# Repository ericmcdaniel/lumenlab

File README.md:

<p align="center">
  <picture>
    <source media="(prefers-color-scheme: dark)" srcset="assets/lumenlab-logo-dark.png">
    <source media="(prefers-color-scheme: light)" srcset="assets/lumenlab-logo.png">
    
  </picture>
</p>
<p align="center">Transforming pixels into a playground</p>

---

__LumenLab__ is an LED strip gaming and entertainment platform designed to transform your space into an interactive playground of light. Powered by an ESP32 microcontroller, displayed through a NeoPixel addressable LED strip, and controlled by a PlayStation 3 game controller, LumenLab brings simple, one-dimensional retro arcade-style games, animations, and ambient lighting to life.
<br>

# Features

LumenLab is composed of two modes. The central mode is its suite of games, but the platform also supports animations and ambient lighting, called scenes. After all it's still an LED strip!

## Games
Using an LED strip as a gaming platform is a unique concept due to the constraint of only having one dimension to interact with. Since *only* the landscape x-axis is available, this constraint compels players to apply creative interpretation during gameplay. This of course is not a modern, feature rich AAA blockbuster with 4K graphics, immersing you in the vision of a world crafted by others. Instead, LumenLab's restriction subtly encourages players to philosophically revisit what it *really* means to play a game down to the core. In its purest form, a game player follows rules and explores boundaries in pursuit of a goal. Gamers encounter conflict and must experiment and adapt to their environment to overcome obstacles. LumenLab forces players to abstractly experience digital gaming at its rawest, most atomic form: structured uncertainty and strategy until mastery is achieved. This has become the manifesto of the LumenLab. **Every individual playing its games has a unique mental concept of what they're experiencing.**

Because LumenLab is restricted to a single dimension composed of an array of LEDs, it's aesthetically reminiscent of retro arcade games. However, LumenLab exploits capabilities unavailable on old 8-bit game consoles. These capabilities include its ability to generate any arbitrary RGB color instead of being limited to 256 colors. Additionally, its UI takes advantage of the broad range of controls and state offered by the PS3 controller such as the number of buttons available and precise analog joy stick/trigger positions, contrasting from a cabinet arcade with only four discrete buttons. There are over six games, each detailed below.

| **Title** | **Description** |
| --- | --- |
| **Recall** | *Recall* is a fast-paced memory game inspired by Hasbro’s classic game [*Simon*](https://en.wikipedia.org/wiki/Simon_(game)). The LED strip flashes a growing sequence of colors, and the player must repeat it correctly using X, Circle, Triangle, and Square buttons of their PS3 controller. |
| **Phase Evasion** | *Phase Evasion* is a fast-paced reflex game where you shift your color to phase through incoming flares. Grab scattered gems for bonus points as the speed increases and the challenge intensifies. |
| **Light Strike** | *Light Strike* combines the spirit of Atari's [*Space Invaders*](https://en.wikipedia.org/wiki/Space_Invaders) with elements of [*Asteroids*](https://en.wikipedia.org/wiki/Asteroids_(video_game)). As a lone agent in deep space, you enounter waves of predators approaching you from directions sides at varying speeds. Moving freely across the x-axis, and your survival requires defending yourself with your laser pistol. Conserve your ammunition however, your weapon can only fire so many rounds a minute!<br><br>*In development.* |
| **Reflex** | *Reflex* is a fast-moving inspired by the modern arcade game [*Pop the Lock*](https://www.baytekent.com/pop-the-lock/), testing precision and timing under pressure. A moving marker sweeps across the field toward a shifting target. Fire at the perfect moment to score a hit. Each success quickens the pace, reverses the marker's direction, and relocates the target to a new random location. Survive fifty flawless shots to win.<br><br>*In development.* |
| **Spectrum** | *Spectrum* tests your perception of color and precision of control. A random RGB color appears on one end of the display, and you must use the analog stick to recreate it as closely as possible. The closer your match, the higher your score.<br><br>*In development* |
| **Pursuit** | *In development.* Details to be provided soon. |

There are more game ideas in the works, and ideas for some *two-player* games are being considered.

## Scenes

An LED strip entertainment platform would not be complete if it did not include animations and special effects libraries. Inspired by the [WLED project](https://kno.wled.ge/), LumenLab is able to create captivating scenes. Many of them are interactive, for example moving the joystick can change the color, or pressing the directional buttons can change timing.
| **Title** | **Description** |
| --- | --- |
| **Canvas** | *Canvas* lets you choose any color across the RGB range, turning the LED strip into a fully color-customized ambient light source. Press **L1** to rebalance the saturation, **R1** to rebalance the lightness, and **Triangle** to switch to a new random color. |
| **Tempo** | *Tempo* allows you to choose a tempo and strobe lights and trigger light subroutines in response to music.<br><br>*In development.* |
| **Police Siren** | Strobing red and blue lights to look like a law enforcement vehicle.<br><br>*In development.* |
| **Halloween** | Spooky orange and some purple.<br><br>*In development.* |
| **Christmas** | Festive red and green.<br><br>*In development.* |

And more to come.

---

# Experience the Lights in Your Home
Being a hardware-forward project, it is not possible to experience LumenLab without physically having the device. Your options include either having a PCB professionally manufactured and assembled, or soldering your own prototype on a breadboard or perf board using off-the-shelf components.

This guide will walk through both options and their practicality.

## Method A: Professionally Manufactured and Assembled

A custom PCB was designed using KiCad 9 and gives LumenLab a clean aesthetic. All of the schematic files, PCB layout files, BOM, custom symbol libraries, footprints, 3D models, and Gerber files are all found in the [/hardware](./hardware/) directory. The PCB layout uses the manufacturing capabilities given by [PCBWay](https://www.pcbway.com/). Although you can potentially use any board house of your choosing, the ECAD model was designed with PCBWay's capabilities in mind. Production costs were minimized as much as safely reasonable, such as keeping it's width under 100mm. However for the amount of current that it can potentially consume, thermal safety was factored in, leading to a four-layer design with extra forgiving trace width and copper pours. My manufacturing costs were roughly $50 for ten boards. If you choose to have this manufactured else where, you must adjust for the capabilities of that board house. Your mileage may vary, and by quite a bit too.

<p align="center"><i>Figure 1: Front of PCB layout</i></p>

You can view the KiCad schematic, PCB layout, BOM, and 3D rendering of the PCB design [in the *board* directory.](./hardware/)

## Method B: Hand-Soldering a Prototype

This is the more accessible and classic route especially for DIY enthusiasts, however this can be tricky depending on your background with electronics. Below is the prototype BOM if you'd like to build LumenLab yourself using pre-built modules, THT components, and a breadboard or perfboard. If you're an advanced electronics enthusiast, you may even be able to omit some of the suggestions, such as skipping the buck converter, directly powering the LED strip, and using the 5V power directly from the Vin pin to level shift the LED strip's data signal. These "barebones" alterations are not discussed in this document.

Assembly is remarkably similar to the guidance given on the WLED project. Using their [wiring diagram here](https://kno.wled.ge/basics/wiring-guides/) would be an excellent starting point.

#### <center>Bill of Materials</center>
|  Device | Description |
| --- | --- |
| ESP32 WROOM microcontroller | Only the [WROOM variants](https://docs.espressif.com/projects/esp-dev-kits/en/latest/esp32/esp32-devkitc/index.html) are supported because those are the only variants that support the Bluetooth classic protocol (BR/EDR). You **cannot** substitude the WROOM with other variants, as they all only have support for BLE. |
| WS2815 LED light strip | The 12V variant of the NeoPixel addressable RGB WS2812B. This project uses the 5m (16.4ft), 300 LED strip in black. |
| 12V 10A DC power supply | The 10A supply is required due to the high current demands of displaying white at full brightness. 120W is only the peak power draw, but this typically runs much lower. |
| MP2338 buck converter | Any step down regulator will suffice as long as it outputs 5V and at least 1A. The MP2338 can deliver 2-3A, enough to reliable power the ESP32 during intense gameplay and Bluetooth connectivity. |
| SN74AHCT125N logic level shifter | The ESP32's GPIO lines work using 3.3V signals. Level shifting to 5V ensures that the LED strip's data lines are not lost or corrupted. |
| PlayStation 3 game controller | The input device to navigate the main menu and play games. |
| SSD1306 OLED display module | Using the 0.96" variant, this displays the main menu for mode selection and in game mode is a HUD showing basic statistic like the user's high score. |
| Passive components | Resistors, capacitors, diodes, and fuses as needed for power protection, power stability and smoothing, low-pass filtering, and signal damping to minimize ringing. Refer to your MCU and buck converter's datasheet for guidance on what passives are needed. |

# Software

Regardless of whether your build of LumenLab was professionally manufactured and assembled, or hand-soldered to a perf board, the software is identical between the two approaches. To build this project from scratch, you at minimum need the following frameworks and dependencies:

* **PlatformIO**: A feature-rich ecosystem for embedded development. This framework includes the C/C++ compiler (avr-gcc) needed for MCU development. You can use the toolchain CLI directly, but installing the Visual Studio Code extension is significantly more approachable. [Download PlatformIO here](https://platformio.org/).
* **Python3** (&GreaterEqual;3.6): A dependency of PlatformIO to compile and flash the device. Also used in the virtualizer for local development.

## LED Strip Virtualization

To streamline the software development cycle, a virtualizer was created so that you can simulate what the LEDs would be displaying, but on your computer screen. This enables new features to be developed in comfort without needing to physically connect to the LED strip. Using the ESP32 is still required for development regardless since it's just an emulator for what the ESP32 is actually doing in real time.

When compiling in debug mode, the ESP32 does not transmit color signals to the LED strip and instead sends its color data via USB serial for virtual rendering. When compiling in release mode, the virtualizer and logs are removed. This virtualizer was created using Python, and uses the [ModernGL](https://moderngl.readthedocs.io/en/5.8.2/) library, an OpenGL binding for Python.

<p align="center"><i>Figure 2: Development Virtualizer of two controllable entities, simulating what the LED strip would be rendering</i></p>

## Building the Repository
This section was redacted temporarily because of how rapidly the code base is evolving. The instructions I wrote no longer apply as the Virtualizer was rewritten for speed to send color data via a USB serial connection instead of an open WebSocket connection. Stay tuned.

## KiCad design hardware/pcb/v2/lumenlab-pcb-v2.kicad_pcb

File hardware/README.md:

# Custom PCB Fabrication

The LumenLab was built in two phases. The first phase (labeled as "Version 1") was a prototype that used through-hole components hand-soldered on to several perf boards. This was a good start, especially for making progress in the early stages of the software development, however the components did not work exactly as desired, making its maintanance more of a hassle than it was a benefit. Designing a PCB to be professionally manufactured became a clear and obvious choice, allowing the LumenLab to be scaled into a clean, stable device.

The LumenLab PCB was designed using KiCad 9.0.5

# Schematic

<p align="center"><i>Figure 1. LumenLab schematic and electronic layout</i></p>

# Bill of Materials
Still to be finalized, however you can [view the tentative list of components here](./v1/bom/ibom.html).

# PCB Layout

<p align="center"><i>Figure 2: PCB layout</i></p>

# 3D Preview

<p align="center"><i>Figure 3: PCB 3D preview</i></p>

A 3D printed enclosure will be created to give the final device a clean look.

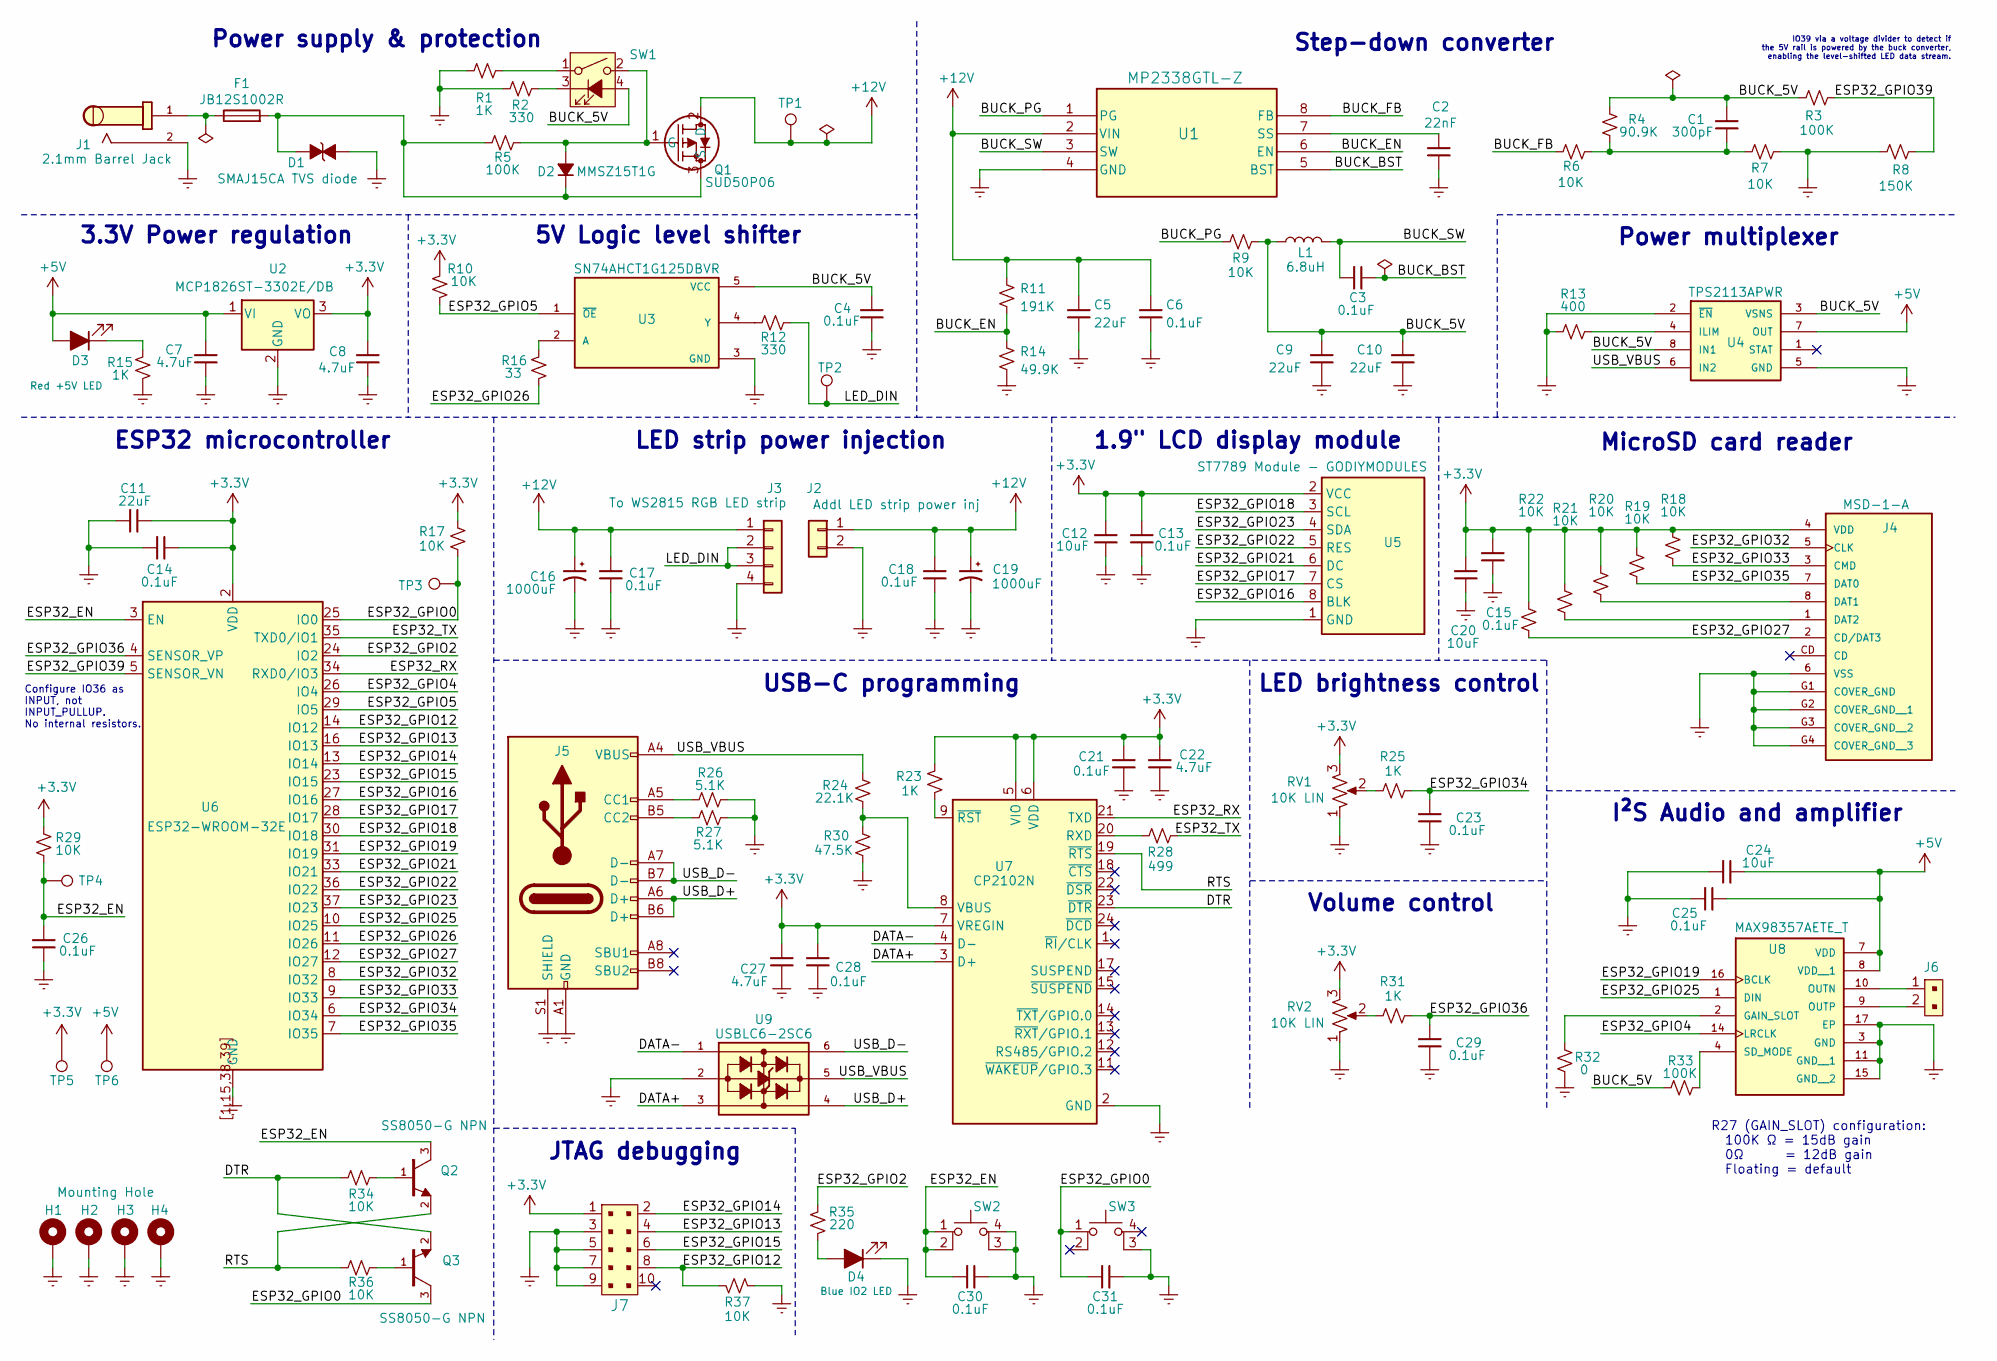
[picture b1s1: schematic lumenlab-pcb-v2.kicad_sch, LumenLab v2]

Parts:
C1: 300pF; C_0603_1608Metric_Pad1.08x0.95mm_HandSolder
C2: 22nF; C_0603_1608Metric_Pad1.08x0.95mm_HandSolder
C3, C4, C6, C13, C14, C15, C17, C18, C21, C23, C25, C26, C28, C29, C30, C31: 0.1uF; C_0603_1608Metric_Pad1.08x0.95mm_HandSolder
C5, C9, C10, C11: 22uF; C_1210_3225Metric_Pad1.33x2.70mm_HandSolder
C7, C8: 4.7uF; C_1206_3216Metric_Pad1.33x1.80mm_HandSolder
C12, C20: 10uF; C_0603_1608Metric_Pad1.08x0.95mm_HandSolder
C16, C19: 1000uF; CP_Radial_D10.0mm_P5.00mm
C22, C27: 4.7uF; C_0805_2012Metric_Pad1.18x1.45mm_HandSolder
C24: 10uF; C_1206_3216Metric_Pad1.33x1.80mm_HandSolder
D1: SMAJ15CA TVS diode; SMASeries_LTF-M
D2: MMSZ15T1G; D_SOD-123
D3: Red +5V LED; LED_0805_2012Metric_Pad1.15x1.40mm_HandSolder
D4: Blue IO2 LED; LED_0805_2012Metric_Pad1.15x1.40mm_HandSolder
F1: JB12S1002R; Fuse_1206_3216Metric_Pad1.42x1.75mm_HandSolder
H1: Mounting Hole; MountingHole_3.2mm_M3_Pad
H2, H3, H4: MountingHole; MountingHole_3.2mm_M3_Pad
J1: 2.1mm Barrel Jack; CONN_SD-172448-0000_02_MOL; PARTREV A
J2: Addl LED strip power inj; CONN_SD-172448-0000_02_MOL
J3: To WS2815 RGB LED strip; CONN_SD-172448-0000_04_MOL
J4: MSD-1-A; CUI_MSD-1-A; PARTREV 1.0
J5: USB_C_Receptacle_USB2.0_16P; USB_C_Receptacle_JAE_DX07S016JA1R1500
J6: B2B-XH-A_LF__SN_; JST_XH_B2B-XH-A_1x02_P2.50mm_Vertical; MPN B2B-XH-A(LF)(SN); Digi-Key_PN 455-2247-ND
J7: JTAG; PinHeader_2x5_P1.27mm_Drill.7mm; MPN 3220-10-0100-00; Digi-Key_PN 1175-1627-ND
L1: 6.8uH; IND_MGAH06036R8M-10
Q1: SUD50P06; PMOSGDS_D-PAKTO-252AA_VIS-L
Q2, Q3: SS8050-G NPN; TRANS_SS8050-G; PARTREV A
R1, R15, R23, R25, R31: 1K; R_0603_1608Metric_Pad0.98x0.95mm_HandSolder
R2, R12: 330; R_0603_1608Metric_Pad0.98x0.95mm_HandSolder
R3, R5, R33: 100K; R_0603_1608Metric_Pad0.98x0.95mm_HandSolder
R4: 90.9K; R_0603_1608Metric_Pad0.98x0.95mm_HandSolder
R6, R7, R9, R10, R17, R18, R19, R20, R21, R22, R29, R34, R36, R37: 10K; R_0603_1608Metric_Pad0.98x0.95mm_HandSolder
R8: 150K; R_0603_1608Metric_Pad0.98x0.95mm_HandSolder
R11: 191K; R_0603_1608Metric_Pad0.98x0.95mm_HandSolder
R13: 400; R_0603_1608Metric_Pad0.98x0.95mm_HandSolder
R14: 49.9K; R_0603_1608Metric_Pad0.98x0.95mm_HandSolder
R16: 33; R_0603_1608Metric_Pad0.98x0.95mm_HandSolder
R24: 22.1K; R_0603_1608Metric_Pad0.98x0.95mm_HandSolder
R26, R27: 5.1K; R_0603_1608Metric_Pad0.98x0.95mm_HandSolder
R28: 499; R_0603_1608Metric_Pad0.98x0.95mm_HandSolder
R30: 47.5K; R_0603_1608Metric_Pad0.98x0.95mm_HandSolder
R32: 0; R_0603_1608Metric_Pad0.98x0.95mm_HandSolder
R35: 220; R_0603_1608Metric_Pad0.98x0.95mm_HandSolder
RV1, RV2: 10K LIN; JST_XH_B3B-XH-A_1x03_P2.50mm_Vertical
SW1: SW_DPST; JST_XH_B4B-XH-A_1x04_P2.50mm_Vertical
SW2: RESET; SW_TS18-5-15-SL-160-SMT-TR
SW3: BOOT; SW_TS18-5-15-SL-160-SMT-TR
TP1: +12V; TestPoint_THTPad_D2.0mm_Drill1.0mm
TP2: LED_SIG; TestPoint_THTPad_D2.0mm_Drill1.0mm
TP3: IO0; TestPoint_THTPad_D2.0mm_Drill1.0mm
TP4: EN; TestPoint_THTPad_D2.0mm_Drill1.0mm
TP5: +3.3V; TestPoint_THTPad_D2.0mm_Drill1.0mm
TP6: +5V; TestPoint_THTPad_D2.0mm_Drill1.0mm
U1: MP2338GTL-Z; MP2338_MNP-M
U2: MCP1826ST-3302E/DB; SOT-223-3_TabPin2
U3: SN74AHCT1G125DBVR; SOT95P280X145-5N
U4: TPS2113APWR; SOP65P640X120-8N
U5: ST7789 Module - GODIYMODULES; JST_XH_B8B-XH-A_1x08_P2.50mm_Vertical
U6: ESP32-WROOM-32E
U7: CP2102N; QFN-24-1EP_4x4mm_P0.5mm_EP2.15x2.15mm
U8: MAX98357AETE_T; QFN50P300X300X80-17N
U9: USBLC6-2SC6; SOT95P280X145-6N

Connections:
+3.3V: C8.1, C11.1, C12.2, C13.2, C14.2, C15.2, C20.2, C21.1, C22.1, C27.1, C28.1, J4.4 (VDD), J7.1, R10.1, R17.1, R18.2, R19.2, R20.2, R21.2, R22.2, R23.2, R29.1, RV1.3, RV2.3, TP5.1 (1_1), U2.3 (VO), U5.2 (VCC), U6.2 (VDD), U7.5 (VIO), U7.6 (VDD), U7.7 (VREGIN)
+5V: C7.1, C24.1, C25.1, D3.2 (A), TP6.1 (1_1), U2.1 (VI), U4.7 (OUT), U8.7 (VDD), U8.8 (VDD__1)
+12V: C5.1, C6.1, C16.1, C17.1, C18.1, C19.1, J2.1, J3.1, Q1.2 (D), R11.1, TP1.1 (1_1), U1.2 (VIN)
/BUCK_5V: C1.2, C4.2, C9.1, C10.1, L1.1, R3.1, R4.2, R9.2, R33.1, SW1.4 (A), U3.5 (VCC), U4.3 (VSNS), U4.8 (IN1)
/BUCK_BST: C3.1, U1.5 (BST)
/BUCK_EN: R11.2, R14.1, U1.6 (EN)
/BUCK_FB: R6.1, U1.8 (FB)
/BUCK_PG: R9.1, U1.1 (PG)
/BUCK_SW: C3.2, L1.2, U1.3 (SW)
/DATA+: U7.3 (D+), U9.3
/DATA-: U7.4 (D-), U9.1
/DTR: Q3.2, R34.1, U7.23 (~DTR)
/ESP32_EN: C26.1, C30.2, Q2.3, R29.2, SW2.1, SW2.2, TP4.1 (1_1), U6.3 (EN)
/ESP32_GPIO0: C31.2, Q3.3, R17.2, SW3.1, TP3.1 (1_1), U6.25 (IO0)
/ESP32_GPIO2: R35.1, U6.24 (IO2)
/ESP32_GPIO4: U6.26 (IO4), U8.14 (LRCLK)
/ESP32_GPIO5: R10.2, U3.1 (~OE), U6.29 (IO5)
/ESP32_GPIO12: J7.8, R37.1, U6.14 (IO12)
/ESP32_GPIO13: J7.4, U6.16 (IO13)
/ESP32_GPIO14: J7.2, U6.13 (IO14)
/ESP32_GPIO15: J7.6, U6.23 (IO15)
/ESP32_GPIO16: U5.8 (BLK), U6.27 (IO16)
/ESP32_GPIO17: U5.7 (CS), U6.28 (IO17)
/ESP32_GPIO18: U5.3 (SCL), U6.30 (IO18)
/ESP32_GPIO19: U6.31 (IO19), U8.16 (BCLK)
/ESP32_GPIO21: U5.6 (DC), U6.33 (IO21)
/ESP32_GPIO22: U5.5 (RES), U6.36 (IO22)
/ESP32_GPIO23: U5.4 (SDA), U6.37 (IO23)
/ESP32_GPIO25: U6.10 (IO25), U8.1 (DIN)
/ESP32_GPIO26: R16.2, U6.11 (IO26)
/ESP32_GPIO27: J4.2 (CD/DAT3), R22.1, U6.12 (IO27)
/ESP32_GPIO32: J4.5 (CLK), U6.8 (IO32)
/ESP32_GPIO33: J4.3 (CMD), R18.1, U6.9 (IO33)
/ESP32_GPIO34: C23.2, R25.2, U6.6 (IO34)
/ESP32_GPIO35: J4.7 (DAT0), R19.1, U6.7 (IO35)
/ESP32_GPIO36: C29.2, R31.2, U6.4 (SENSOR_VP)
/ESP32_GPIO39: R3.2, R8.1, U6.5 (SENSOR_VN)
/ESP32_RX: U6.34 (RXD0/IO3), U7.21 (TXD)
/ESP32_TX: R28.1, U6.35 (TXD0/IO1)
/LED_DIN: J3.2, J3.3, R12.2, TP2.1 (1_1)
/RTS: Q2.2, R36.1, U7.19 (~RTS)
/USB_D+: J5.A6 (D+), J5.B6 (D+), U9.4
/USB_D-: J5.A7 (D-), J5.B7 (D-), U9.6
/USB_VBUS: J5.A4 (VBUS), J5.A9 (VBUS), J5.B4 (VBUS), J5.B9 (VBUS), R24.1, U4.6 (IN2), U9.5
GND: C2.1, C4.1, C5.2, C6.2, C7.2, C8.2, C9.2, C10.2, C11.2, C12.1, C13.1, C14.1, C15.1, C16.2, C17.2, C18.2, C19.2, C20.1, C21.2, C22.2, C23.1, C24.2, C25.2, C26.2, C27.2, C28.2, C29.1, C30.1, C31.1, D1.1, D4.1 (K), H1.1 (1_1), H2.1 (1_1), H3.1 (1_1), H4.1 (1_1), J1.2, J2.2, J3.4, J4.6 (VSS), J4.G1 (COVER_GND), J4.G2 (COVER_GND__1), J4.G3 (COVER_GND__2), J4.G4 (COVER_GND__3), J5.A1 (GND), J5.A12 (GND), J5.B1 (GND), J5.B12 (GND), J5.S1 (SHIELD), J7.3, J7.5, J7.7, J7.9, R1.1, R2.1, R7.2, R8.2, R13.1, R14.2, R15.2, R26.2, R27.2, R30.1, R32.2, R37.2, RV1.1, RV2.1, SW2.3 (K), SW2.4 (A), SW3.3 (K), U1.4 (GND), U2.2 (GND), U3.3 (GND), U4.2 (~EN), U4.5 (GND), U5.1 (GND), U6.1 (GND), U6.15 (GND), U6.38 (GND), U6.39 (GND), U6.[1,15,38,39] (GND), U7.2 (GND), U7.25 (GND), U8.3 (GND), U8.11 (GND__1), U8.15 (GND__2), U8.17 (EP), U9.2
unnamed: C1.1, R4.1, R6.2, R7.1
unnamed: D2.2 (A), Q1.1 (G), R5.2, SW1.2
unnamed: D1.2, D2.1 (K), F1.2, Q1.3 (S), R5.1
unnamed: D3.1 (K), R15.1
unnamed: D4.2 (A), R35.2
unnamed: F1.1, J1.1
unnamed: J4.8 (DAT1), R20.1
unnamed: J4.1 (DAT2), R21.1
unnamed: J5.A5 (CC1), R26.1
unnamed: J5.B5 (CC2), R27.1
unnamed: Q2.1, R34.2
unnamed: Q3.1, R36.2
unnamed: R1.2, SW1.1
unnamed: R25.1, RV1.2
unnamed: R31.1, RV2.2
unnamed: R2.2, SW1.3 (K)
unnamed: C2.2, U1.7 (SS)
unnamed: R16.1, U3.2 (A)
unnamed: R12.1, U3.4 (Y)
unnamed: R13.2, U4.4 (ILIM)
unnamed: R28.2, U7.20 (RXD)
unnamed: R24.2, R30.2, U7.8 (VBUS)
unnamed: R23.1, U7.9 (~RST)
unnamed: R32.1, U8.2 (GAIN_SLOT)
unnamed: J6.1, U8.10 (OUTN)
unnamed: J6.2, U8.9 (OUTP)
unnamed: R33.2, U8.4 (SD_MODE)

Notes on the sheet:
LED brightness control
Configure IO36 as INPUT, not INPUT_PULLUP. No internal resistors.
JTAG debugging
Power multiplexer
Power supply & protection
R27 (GAIN_SLOT) configuration: 100K Ω = 15dB gain 0Ω = 12dB gain Floating = default
LED strip power injection
Step-down converter
USB-C programming
Volume control
ESP32 microcontroller
5V Logic level shifter
MicroSD card reader
I²S Audio and amplifier
3.3V Power regulation
IO39 via a voltage divider to detect if the 5V rail is powered by the buck converter, enabling the level-shifted LED data stream.
1.9" LCD display module

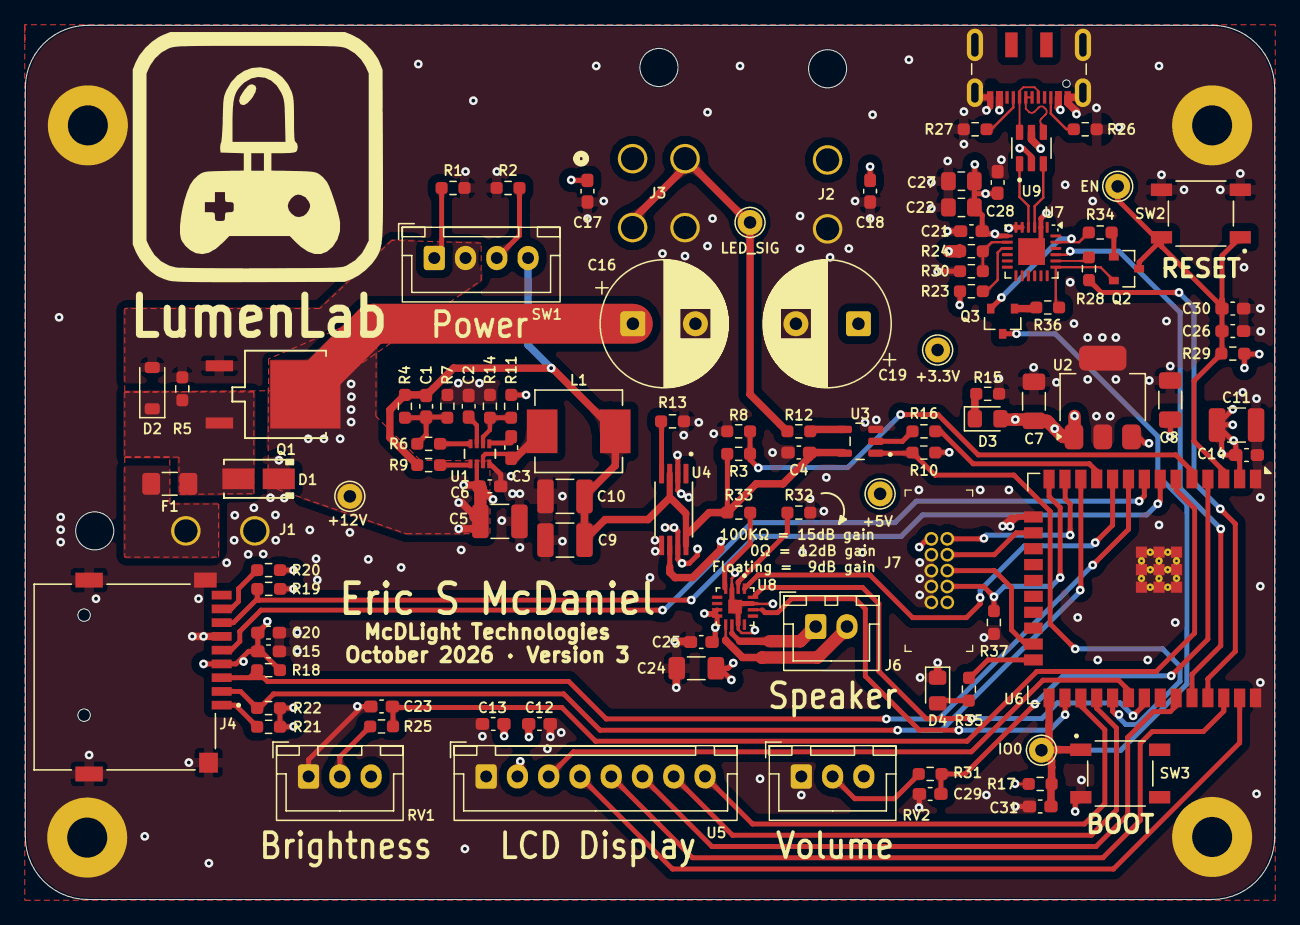
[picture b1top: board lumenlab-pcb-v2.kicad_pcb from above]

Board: 4 copper layers, 99.9 x 69.9 mm, 108 parts (0 on the bottom side), 72 nets.

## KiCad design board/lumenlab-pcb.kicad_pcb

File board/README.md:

# Custom PCB Fabrication

The LumenLab was built in two phases. The first phase (labeled as "Version 1") was a prototype that used through-hole components hand-soldered on to several perf boards. This was a good start, especially for making progress in the early stages of the software development, however the components did not work exactly as desired, making its maintanance more of a hassle than it was a benefit. Designing a PCB to be professionally manufactured became a clear and obvious choice, allowing the LumenLab to be scaled into a clean, stable device.

The LumenLab PCB was designed using KiCad 9.0.5

# Schematic

<p align="center">Figure 1. LumenLab schematic and electronic layout</p>

# Bill of Materials
Still to be finalized, however you can [view the tentative list of components here](./bom/ibom.html).

# PCB Layout

<p align="center"><i>Figure 2: PCB layout</i></p>

# 3D Preview

<p align="center"><i>Figure 3: PCB 3D preview (front)</i></p>

<p align="center"><i>Figure 4: PCB 3D preview (back)</i></p>

A 3D printed enclosure will be created to give the final device a clean look.

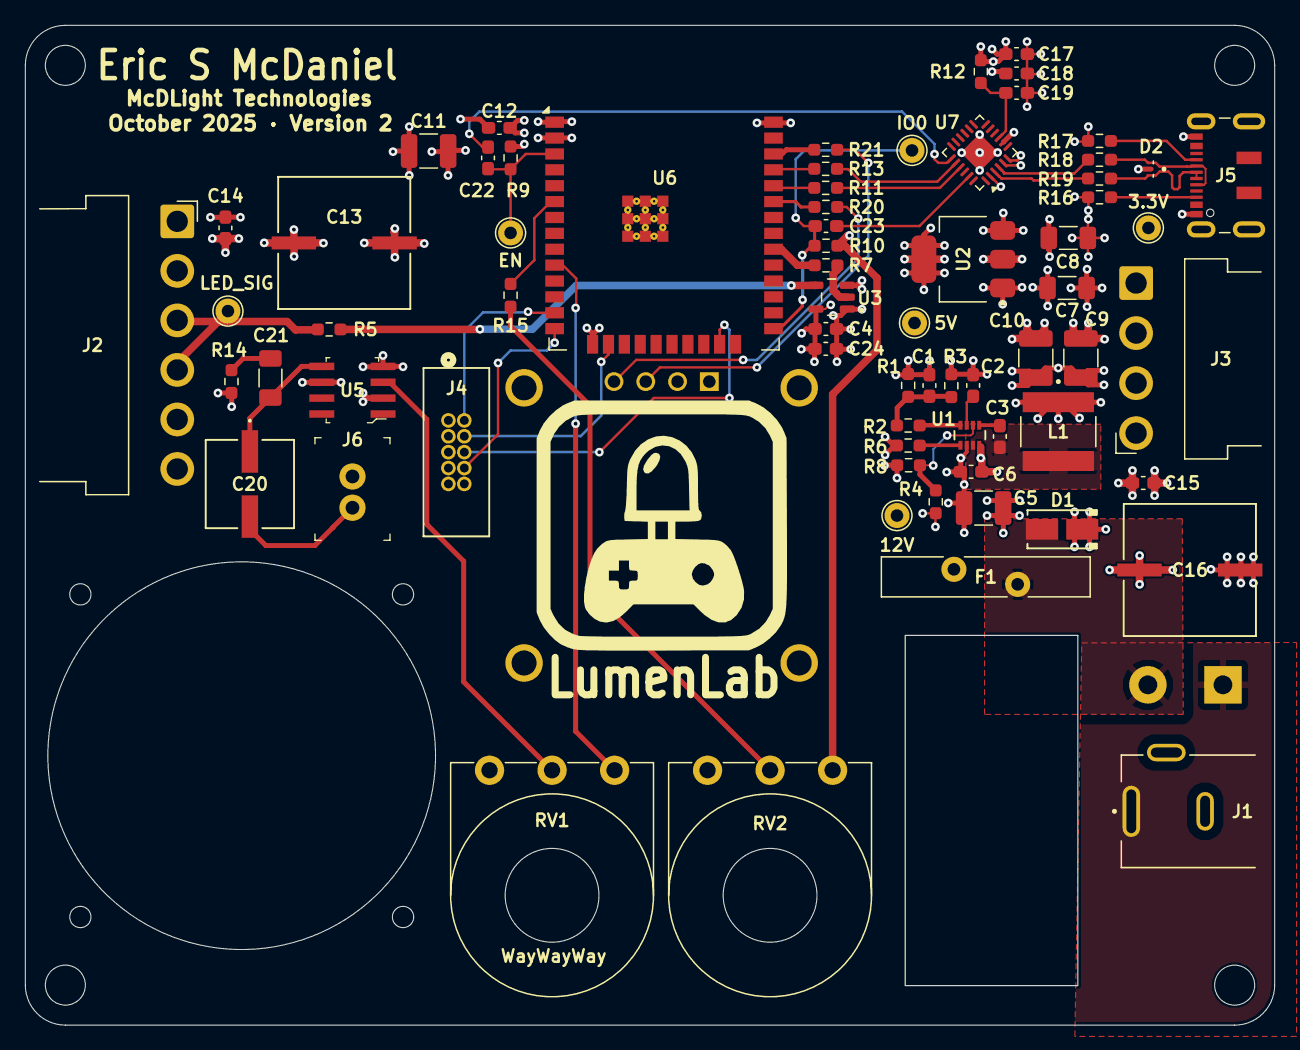
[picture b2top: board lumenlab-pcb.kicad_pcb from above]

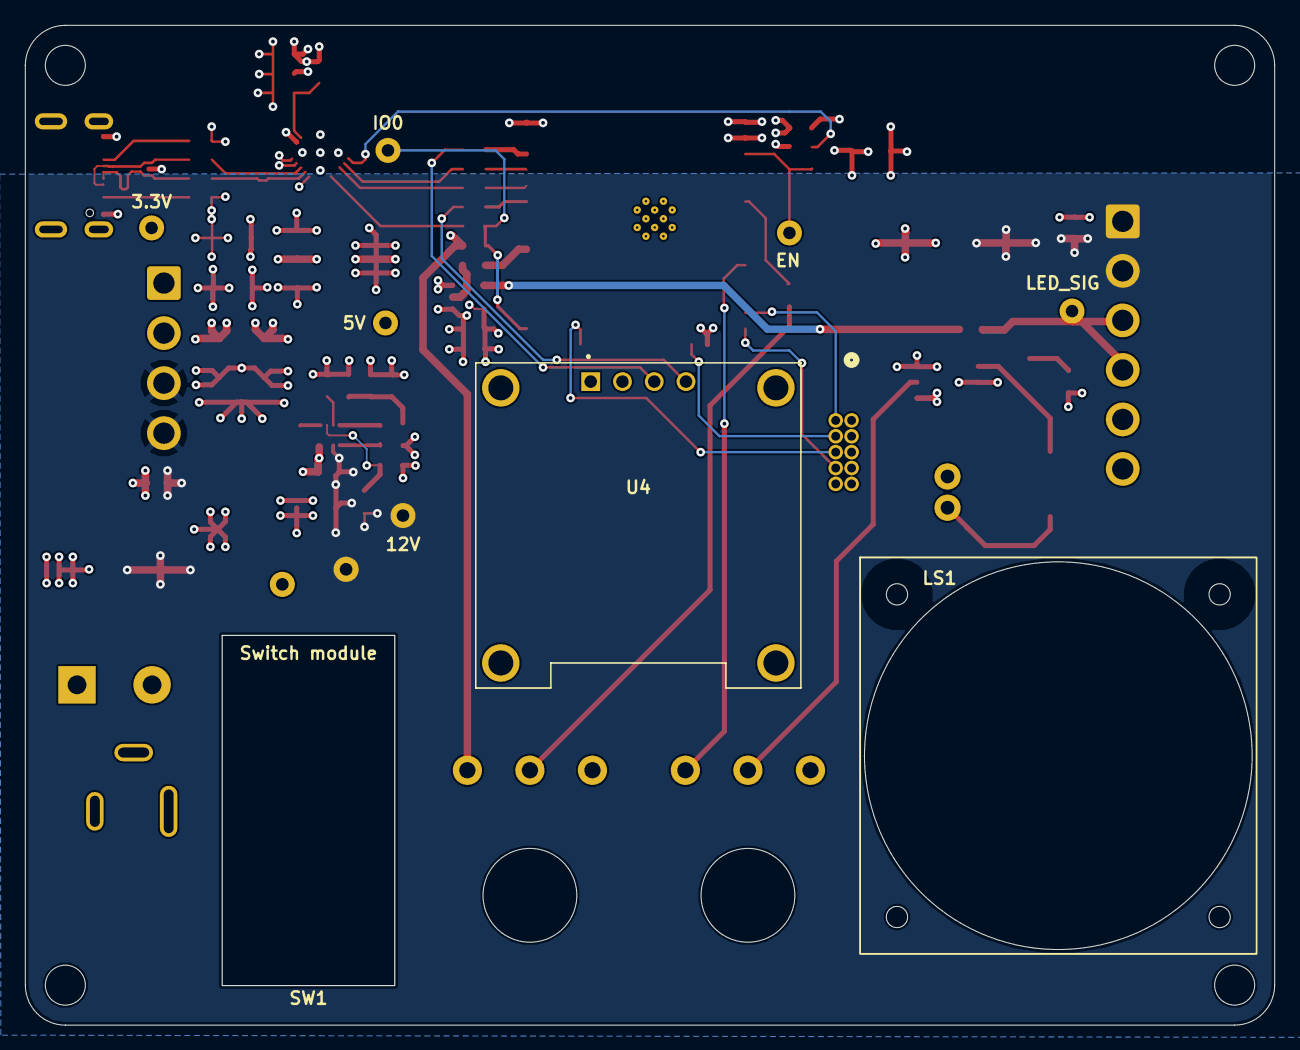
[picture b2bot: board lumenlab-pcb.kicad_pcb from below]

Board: 4 copper layers, 99.9 x 79.9 mm, 76 parts (3 on the bottom side), 47 nets.

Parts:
C1: 300pF; C_0603_1608Metric_Pad1.08x0.95mm_HandSolder
C2: 22nF; C_0603_1608Metric_Pad1.08x0.95mm_HandSolder
C3, C4, C6, C12, C14, C15, C17, C18, C19, C22, C23, C24: 0.1uF; C_0603_1608Metric_Pad1.08x0.95mm_HandSolder
C5, C9, C10, C11: 22uF; C_1210_3225Metric_Pad1.33x2.70mm_HandSolder
C7, C8: 4.7uF; C_1206_3216Metric_Pad1.33x1.80mm_HandSolder
C13, C16: 1000uF; CAP_JA0_NIP
C20: 250uF; CAP_J-V_6P3X8_RUB-M
C21: 0.05uF; C_1206_3216Metric_Pad1.33x1.80mm_HandSolder
D1: SMAJ12CA; SMASeries_LTF-M
D2: ESD122DMYR; DIO_ESD122DMYR
F1: Polyfuse; Fuse_Bourns_MF-RG1000
H1, H2, H3, H4: MountingHole; MountingHole_3.2mm_M3
J1: 2.1mm Barrel Jack; 2_Vendor_BarrelJack
J2: 01x06; JST_VH_1x06_P3.96_SilkscreenTrimmed
J3: 01x04; JST_VH_1x04_P3.96mm_SilkscreenTrimmed
J4: JTAG; JTAG-header
J5: USB_C_Receptacle_USB2.0_16P; USB_C_Receptacle_JAE_DX07S016JA1R1500
J6: B2B-XH-A_LF__SN_; PinHeader_1x2_P2.5mm_Drill1.1mm
L1: 6.8uH; IND_1264EY-6R8M=P3
LS1: Speaker
R1: 90.9K; R_0603_1608Metric_Pad0.98x0.95mm_HandSolder
R2, R3, R6, R9, R10, R12: 10K; R_0603_1608Metric_Pad0.98x0.95mm_HandSolder
R4: 191K; R_0603_1608Metric_Pad0.98x0.95mm_HandSolder
R5: 330; R_0603_1608Metric_Pad0.98x0.95mm_HandSolder
R7: 33; R_0603_1608Metric_Pad0.98x0.95mm_HandSolder
R8: 49.9K; R_0603_1608Metric_Pad0.98x0.95mm_HandSolder
R11, R13, R15: 1K; R_0603_1608Metric_Pad0.98x0.95mm_HandSolder
R14: 10; R_0603_1608Metric_Pad0.98x0.95mm_HandSolder
R16, R17: 5.1K; R_0603_1608Metric_Pad0.98x0.95mm_HandSolder
R18, R19: 22; R_0603_1608Metric_Pad0.98x0.95mm_HandSolder
R20, R21: 4.7K; R_0603_1608Metric_Pad0.98x0.95mm_HandSolder
RV1: 10K LOG; Potentiometer
RV2: 10K LIN; Potentiometer
SW1: SW_SPST; RockerPowerSwitch
TP1: 12V; TestPoint_THTPad_D2.0mm_Drill1.0mm
TP2: EN; TestPoint_THTPad_D2.0mm_Drill1.0mm
TP3: IO0; TestPoint_THTPad_D2.0mm_Drill1.0mm
TP4: 3.3V; TestPoint_THTPad_D2.0mm_Drill1.0mm
TP5: 5V; TestPoint_THTPad_D2.0mm_Drill1.0mm
TP6: LED_SIG; TestPoint_THTPad_D2.0mm_Drill1.0mm
U1: MP2338; MP2338_MNP-M
U2: AP7361C-33E; SOT-223-3_TabPin2
U3: SN74AHCT1G125; SOT95P280X145-5N
U4: SSD1306; SSD1306_OLED_MODULE
U5: LM386MX; SOIC-8_W3.9mm
U6: ESP32-WROOM-32E; ESP32_WROOM_32E
U7: CP2102N-Axx-xQFN24; QFN-24-1EP_4x4mm_P0.5mm_EP2.15x2.15mm

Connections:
+3.3V: C8.1, C11.2, C12.1, C17.1, C18.1, R9.1, R10.1, R12.2, RV2.3, TP4.1, U2.3 (VO), U6.2 (VDD), U7.5 (VIO), U7.6 (VDD)
+5V: C1.2, C4.2, C7.1, C9.1, C10.1, C24.1, J4.1, L1.1, R1.2, R6.2, TP5.1, U2.1 (VI), U3.5 (VCC), U4.2 (VCC), U5.6, U7.8 (VBUS)
+12V: C5.1, C6.1, C13.1, C14.1, C15.1, C16.1, F1.2, J2.1, J2.2, J3.3, J3.4, R4.1, TP1.1, U1.2 (VIN)
/AMP_IN: RV1.2, U5.3
/BUCK_BST: C3.1, U1.5 (BST)
/BUCK_EN: R4.2, R8.1, U1.6 (EN)
/BUCK_FB: R2.1, U1.8 (FB)
/BUCK_PG: R6.1, U1.1 (PG)
/BUCK_SS: C2.2, U1.7 (SS)
/BUCK_SW: C3.2, L1.2, U1.3 (SW)
/DATA+: R19.2, U7.3 (D+)
/DATA-: R18.2, U7.4 (D-)
/ESP32_EN: C22.2, R9.2, TP2.1, U6.3 (EN)
/ESP32_GPIO0: C23.2, R10.2, TP3.1, U6.25 (IO0)
/ESP32_GPIO12: J4.8, U6.14 (IO12)
/ESP32_GPIO13: J4.4, U6.16 (IO13)
/ESP32_GPIO14: J4.2, U6.13 (IO14)
/ESP32_GPIO15: J4.6, U6.23 (IO15)
/ESP32_GPIO18: R7.2, U6.30 (IO18)
/ESP32_GPIO21: R20.1, U6.33 (IO21)
/ESP32_GPIO22: R21.1, U6.36 (IO22)
/ESP32_GPIO25: RV1.3, U6.10 (IO25)
/ESP32_GPIO34: R15.2, U6.6 (IO34)
/ESP32_RX: R11.2, U6.34 (RXD0/IO3)
/ESP32_TX: R13.2, U6.35 (TXD0/IO1)
/FUSE: D1.2, F1.1, SW1.2 (B)
/LED_DIN: J2.3, J2.4, R5.2, TP6.1
/USB_D+: D2.3, J5.A6 (D+), J5.B6 (D+), R19.1
/USB_D-: D2.2, J5.A7 (D-), J5.B7 (D-), R18.1
GND: C2.1, C4.1, C5.2, C6.2, C7.2, C8.2, C9.2, C10.2, C11.1, C12.2, C13.2, C14.2, C15.2, C16.2, C17.2, C18.2, C19.2, C24.2, D1.1, D2.1, J1.2, J1.3, J2.5, J2.6, J3.1, J3.2, J4.3, J4.5, J4.7, J4.9, J5.A1 (GND), J5.A12 (GND), J5.B1 (GND), J5.B12 (GND), J6.2, R3.2, R8.2, R14.1, R16.2, R17.2, RV1.1, RV2.1, U1.4 (GND), U2.2 (GND), U3.1 (~OE), U3.3 (GND), U4.1 (GND), U5.2, U5.4, U6.1 (GND), U6.15 (GND), U6.38 (GND), U6.39 (GND), U7.2 (GND), U7.25 (GND)
unnamed: C1.1, R1.1, R2.2, R3.1
unnamed: C20.1, C21.1, U5.5
unnamed: C20.2, J6.1
unnamed: C21.2, R14.2
unnamed: J5.A5 (CC1), R16.1
unnamed: J5.B5 (CC2), R17.1
unnamed: R15.1, RV2.2
unnamed: J1.1, SW1.1 (A)
unnamed: R7.1, U3.2 (A)
unnamed: R5.1, U3.4 (Y)
unnamed: R21.2, U4.3 (SCL)
unnamed: R20.2, U4.4 (SDA)
unnamed: R13.1, U7.20 (RXD)
unnamed: R11.1, U7.21 (TXD)
unnamed: C23.1, U7.23 (~DTR)
unnamed: C19.1, R12.1, U7.9 (~RST)
unnamed: C22.1, U7.19 (~RTS)

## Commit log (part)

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2025-11-06 Fix error when triggered on repeat colors
2025-11-07 Refactor boundary selection
2025-11-07 Add main menu navigation feedback
2025-11-07 Add games menu navigation feedback
2025-11-07 Add blur effect
2025-11-08 Fix round transition after last guess
2025-11-08 Add blended edges
2025-11-09 Add fadeaway after successful round
2025-11-11 Convert FastLED CRGB to Color
2025-11-11 Add helper methods
2025-11-12 Refine colors and convenience methods
2025-11-12 Remove unnecessary dependencies
2025-11-13 Add gameplay speed control
2025-11-15 Add Scenes menu navigation
2025-11-15 Setup Canvas core module and state
2025-11-17 Implement HSL conversion class
2025-11-17 Remove temp lib, setup canvas
2025-11-18 Direct accessor for r, g, & b
2025-11-18 Convert float to double
2025-11-19 Make Color adjustable with controller
2025-11-19 Add ability to change to random color
2025-11-20 Add rebalance/reset option
2025-11-21 Fine-tune Recall's timing, add instructions to docs
2025-11-25 Set currentColor by global state manager
2025-11-25 Trigger OLED display only after button release
2025-11-25 Update OLED display on color change
2025-11-26 Rename Sandbox/Testing to Demo
2025-11-27 Setup Phase Evasion context manager
2025-11-27 Make Phase Evasion playable on menu navigation
2025-11-27 Trigger OLED display visibility on/off
2025-11-28 Add debounce to display visibility
2025-11-28 Globally refactor button debounce
2025-11-28 Fix Recall illumination timing
2025-11-29 Add install script
2025-11-29 Add CICD image push to registry
2025-11-29 Add installation guide
2025-11-29 Fix pixel overlap
2025-11-30 Tune the game control precision
2025-12-01 Setup for physical light debut, stack allocate Player
2025-12-01 Standardize game controller colors
2025-12-02 Rearrange parameter to match physical setup
2025-12-06 Start enclosure
2025-12-06 Set KiCad origin
2025-12-06 Add checklist for microsoldering
2025-12-06 Add wall thickness for enclosure lid
2025-12-06 Fix slit dimensions for SPST power switch
2025-12-06 Add mounts for front face
2025-12-06 Modify sketch face
2025-12-06 Add lip around front face
2025-12-06 Add through-holes for potentiometers and SPST switch
2025-12-06 Widen OLED display pocket
2025-12-07 Additional fit adjustment for OLED display
2025-12-18 Adjust HSL/RGB conversions
2025-12-19 Restore saturation and hue shift for screen-based development
2026-01-03 Revert "Merge pull request #27 from ericmcdaniel/engine/color-correction"
    This reverts commit 62b01568730847356b4a8409d70c1d33c7528796, reversing
    changes made to d1a8a9e5cdb33f83ad9aee897295abea15506cd3.
2026-01-09 Add gamma and gain correction
2026-01-09 Fine tune gain
2026-01-10 Fix game over spin
2026-01-12 Passive components value adjustments for stronger signal comm
2026-01-12 Add outline for enclosure body
2026-01-12 Chamfer rough edges
2026-01-12 Add remaining pockets for power/injection
2026-01-12 Adjust cap side length
2026-01-12 Set back lid size to fit components, open port for LED socket
2026-01-12 Minor fit adjustments
2026-01-12 Add mounting hole, adjust dimensions
2026-01-12 Widen inner lip for looser fit
2026-01-12 Start logo on lid face
2026-01-12 Finishing filets, chamfers, and screw sizes
2026-01-12 Mounting improvement
2026-01-14 Adjust side clearance
2026-01-15 Add outline around LED
2026-01-16 Create production files and docs
2026-01-16 Setup Phase Evasion state machine
2026-01-16 Render user color
2026-01-16 Setup flare and position updating
2026-01-17 Trigger game ending on collision
2026-01-20 Create FlareManager data structure to orchestrate multiple flares
2026-01-20 Add precision in flare speed
2026-01-21 Setup loop over FlareManager
2026-01-21 Reduce data required for Flare construction
2026-01-21 Random color flare dispatch
2026-01-23 Phase Evasion namespace
2026-01-23 Phase Evasion file system refresh
2026-01-23 Move Config to Core module
2026-01-24 Recall namespace
2026-01-24 Demo namespace
2026-01-24 Canvas namespace
2026-01-24 Vector to Array DS change
2026-01-27 Manager controls Flare config
2026-01-30 MLP, playable
2026-01-31 Increment score as flares complete cycle
2026-01-31 Consistent nomenclature
2026-01-31 Fine tune game start settings
2026-02-02 Remove hiccup at start
2026-02-03 Centralize available buttons source
2026-02-03 Setup quick replay when game is over
2026-02-03 Create wind-down breaks between rounds
2026-02-03 Set wind down timing tweaks
2026-02-04 Add muzzle flash
2026-02-05 Disallow wrap around for Phase Evasion
2026-02-05 System wide dependency cleanup
2026-02-05 Add gem capture
2026-02-05 Focus GameOver lights on collision site
2026-02-06 Set timeout for gem before respawn
2026-02-06 calculate HUD adjusted totals and high score
2026-02-07 Setup core design of new discrete menu tiles
2026-02-07 Consistent color themes
2026-02-07 Adjust submenu selection based on highlighted main menu
2026-02-07 Compute gaussian curve for blended menu tiles
2026-02-08 Architectural refactor (single-responsibility)
2026-02-09 Adjust spacing, refactor
2026-02-10 Programatically calculate total and high score
2026-02-10 Preferences memory setup
2026-02-11 Manage menu tile brightness
2026-02-11 Set high score Recall logic
2026-02-11 Control when to write high score
2026-02-11 Display high score on OLED screen
2026-02-11 Refactor high score calc ownership
2026-02-11 Ensure score resets on game change, bump to C++20
2026-02-13 Add stages for build, test, and deployment
2026-02-14 Add GitHub token
2026-02-14 Split triggers into two pipelines
2026-02-14 Fix incorrect parse
2026-02-16 Append version number to firmware.bin
2026-02-16 Move version number to .data segment
2026-02-19 Set system config from Preferences
2026-02-19 Set configuration for boundaries/dimensions
2026-02-19 Fix dimensions call
2026-02-21 Fix data type cast mismatch
2026-02-22 Remove unnecessary boundary
2026-02-24 Combine embedded bindings with NVS memory
2026-02-24 Fix build order
2026-02-25 Replace overwritten file
2026-02-26 Add PS4 lib, set build flag for PS3
2026-02-27 Dependency management
2026-02-27 Replace PS4 lib, add guards
2026-02-28 Fix bug with high score, buffer size
2026-02-28 Extract persistent memory initialization
2026-02-28 First multi-target build with different controllers
2026-03-01 Fix runtime crash on PS3 controller init
2026-03-01 Multi-target build directives
2026-03-01 Add missing header guard
2026-03-03 Setup multi-target build tasks for local development
2026-03-03 Create ci/cd pipeline for multi-artifact deployment
2026-03-05 Map PS4 buttons, fix initialization
2026-03-06 Disable PS4 controller release in pipeline
2026-03-06 Fix non-existent build directory
2026-03-15 Start in-deptch game documentation
2026-03-15 Add 'how to play' instructions for Recall
2026-03-15 Add summary for Phase Evasion
2026-03-15 Add gameplay controls for Phase Evasion
2026-03-21 Setup of rumble task
2026-03-21 Complete controller rumble api
2026-03-21 Add rumble to all supported games
2026-03-21 Add rumble to base Controller class for future PS4 support
2026-03-21 Standardize NVS naming format
2026-03-21 Add games menu pagination
2026-03-21 Add menu tile
2026-03-21 Start module for Chain Reaction
2026-03-21 Create Ion and resource manager
2026-03-21 Startup Chain Reaction
2026-03-23 Setup sketch of led strip bracket
2026-03-23 Calculate width spacing
2026-03-24 Add seat for acrylic sheet
2026-03-24 Add rail for support
2026-03-24 Complete rough mount/bracket
2026-03-24 Add joints
2026-03-24 Adjust clearances, prototype-print ready
2026-03-25 Add snap-fit joints for acrylic fit
2026-03-25 Add model image and description
2026-03-26 Add endcap, mating connection, experiment with geometries
2026-03-26 Align endcap
2026-03-27 Tighten tolerance for mating guide pin, add acrylic snap fit
2026-03-28 Add pivot for 135-degree turn
2026-03-28 Fix extrusion angle
2026-03-31 Modular face plate for rounded edges
2026-03-31 Update doc image
2026-04-01 Restore solids due to white light absorbtion
2026-04-01 Set globals
2026-04-02 Standardize faceplate height
2026-04-02 Export models, add images
2026-04-04 Add lid for new enclosure
2026-04-04 Add profile for curved edge on body
2026-04-04 Bump model to FC v1.1
2026-04-04 Add speaker cutout
2026-04-05 Add controller saddle
2026-04-07 Secure snap fit, add input cutout
2026-04-08 Move speaker for PCB clearance
2026-04-08 Move/center logo outline
2026-04-11 Additional fit adjustments after first print
2026-04-11 Add strength to bottom clamp
2026-04-11 Add branding to left side
2026-04-14 Add CAD image to docs
2026-04-14 Add fillet finishes to CAD model
2026-04-14 Add CAD models for export
2026-04-17 Rotate enclosure
2026-04-18 Remove threaded insert from lid, add through-hole
2026-04-18 Move 5mm threaded insert to body
2026-04-18 Adjust counterbore diameter, resize/move speaker honeycomb
2026-04-18 Extend air vents for better circulation
2026-04-18 Fix broken chamfer
2026-04-20 Setup curved angle of the bracket
2026-04-20 Extrude, controller backing
2026-04-20 Carve LED shape into mount
2026-04-21 Import PS3 model for reference geometry
2026-04-21 Sketch saddle
2026-04-21 Run BOPCheck in Check Geometry
2026-04-21 Add curved saddle
2026-04-22 Create LED bracket shape
2026-04-23 Adjust for poorly scaled reference model
2026-04-24 Add support profile
2026-04-24 Add rear curve, fillet
2026-04-25 Fix model broken from topological naming problem
2026-04-25 Reshape and add LED shape design
2026-04-26 Fillet edges, add image to docs
2026-04-26 Strengthen clip
2026-04-27 Refine snap-fit
2026-04-27 Fit tweaks, strong snap fit, finishing touches
2026-04-28 Refine connector for power
2026-04-28 Add cutout for LED output
2026-04-30 Smoothen sharp edges
2026-05-01 Setup inter-locking snap mechanism
2026-05-02 Lengthen mating pin for alignment
2026-05-02 Ensure mating pin clearances is tight fit
2026-05-02 Adjust bracket shape to reduce amount of diffuser sheets needed
2026-05-04 Add M4 heat set inserts
2026-05-04 Start clip
2026-05-05 Widen lip
2026-05-06 Thicken lip for strength
2026-05-06 Add raw geometry of saddle for finishing vinyl center support
2026-05-08 Get raw working portotype of the rail clamp
2026-05-08 Thicken walls, final model for first print
2026-05-09 Fix sizing issue after first test print
2026-05-09 Add wider rail for acrylic diffuser
2026-05-10 Add endcap for widened rai[
2026-05-11 Add mirror and endcap for connection reversal
2026-05-14 Add friction detent to hold acrylic panel snug
2026-05-14 Adjust width after test print
2026-05-14 Additional fit test, loosened
2026-05-16 Fix linear pattern for LED cavity fillet
2026-05-16 Export general purpose models
2026-05-16 Update documentation, add images for reference
2026-05-19 Strengthen enclosure strength, make micro adjustments to port sizing
2026-05-20 Fix scale functions, add addl mounting points
2026-05-21 Modularize colored print objects
    19 hour print job reduced to 9 hours
2026-05-22 Shrink LED cell size after connecting multiple test prints
2026-05-30 Fix extruded connector pins in endcap
2026-06-04 Include resized 4px to 2px
2026-06-08 Add mounting guide for installation
2026-06-20 Add image collage from physical print
2026-06-22 Add ion dispatch and ion render
2026-06-22 Setup state and startup
2026-06-22 Refine ion manager
2026-06-22 Setup reset
2026-06-22 Ensure dev doesn't depend on live GPIO reads
2026-06-22 Render ion correctly
2026-06-22 Add missing chamfer
2026-06-22 Override GPIO read for standardized development
2026-06-22 Complete system support for new app
2026-06-23 Setup rough debugger for OLED display
2026-06-23 Update display on Reflex start
2026-06-24 Remove redundant includes
2026-06-24 Create Signal entity
2026-06-25 Define signal attributes, render first animation
2026-06-27 Start new Renderer, restructure layer as application
2026-06-28 Migrate led obj to the renderer, setup for refactor
2026-06-29 Restructure platform
2026-06-30 Support for alpha channel
2026-06-30 Property swap alpha for layer
    alpha is to be handled by the renderer during compositing
2026-06-30 Move remaining core to platform
2026-06-30 Scale data structure replacement for chain replacement
